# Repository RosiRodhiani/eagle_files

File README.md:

eagle_files
===========

THE SOFTWARE IS PROVIDED "AS IS", WITHOUT WARRANTY OF ANY KIND, EXPRESS OR IMPLIED, INCLUDING BUT NOT LIMITED TO THE WARRANTIES OF MERCHANTABILITY, FITNESS FOR A PARTICULAR PURPOSE AND NONINFRINGEMENT. IN NO EVENT SHALL THE AUTHORS OR COPYRIGHT HOLDERS BE LIABLE FOR ANY CLAIM, DAMAGES OR OTHER LIABILITY, WHETHER IN AN ACTION OF CONTRACT, TORT OR OTHERWISE, ARISING FROM, OUT OF OR IN CONNECTION WITH THE SOFTWARE OR THE USE OR OTHER DEALINGS IN THE SOFTWARE.

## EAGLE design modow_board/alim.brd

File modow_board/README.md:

A board I made for the french robotics cup of 2016 (beachbots).
It uses a Nucleo (stm32) as (mother board', the rest is mainly power and digital analog I/O.

The PRODUCT IS PROVIDED "AS IS", WITHOUT WARRANTY OF ANY KIND, EXPRESS OR IMPLIED, INCLUDING BUT NOT LIMITED TO THE WARRANTIES OF MERCHANTABILITY, FITNESS FOR A PARTICULAR PURPOSE AND NONINFRINGEMENT. IN NO EVENT SHALL THE AUTHORS OR COPYRIGHT HOLDERS BE LIABLE FOR ANY CLAIM, DAMAGES OR OTHER LIABILITY, WHETHER IN AN ACTION OF CONTRACT, TORT OR OTHERWISE, ARISING FROM, OUT OF OR IN CONNECTION WITH THE SOFTWARE OR THE USE OR OTHER DEALINGS IN THE PRODUCT.

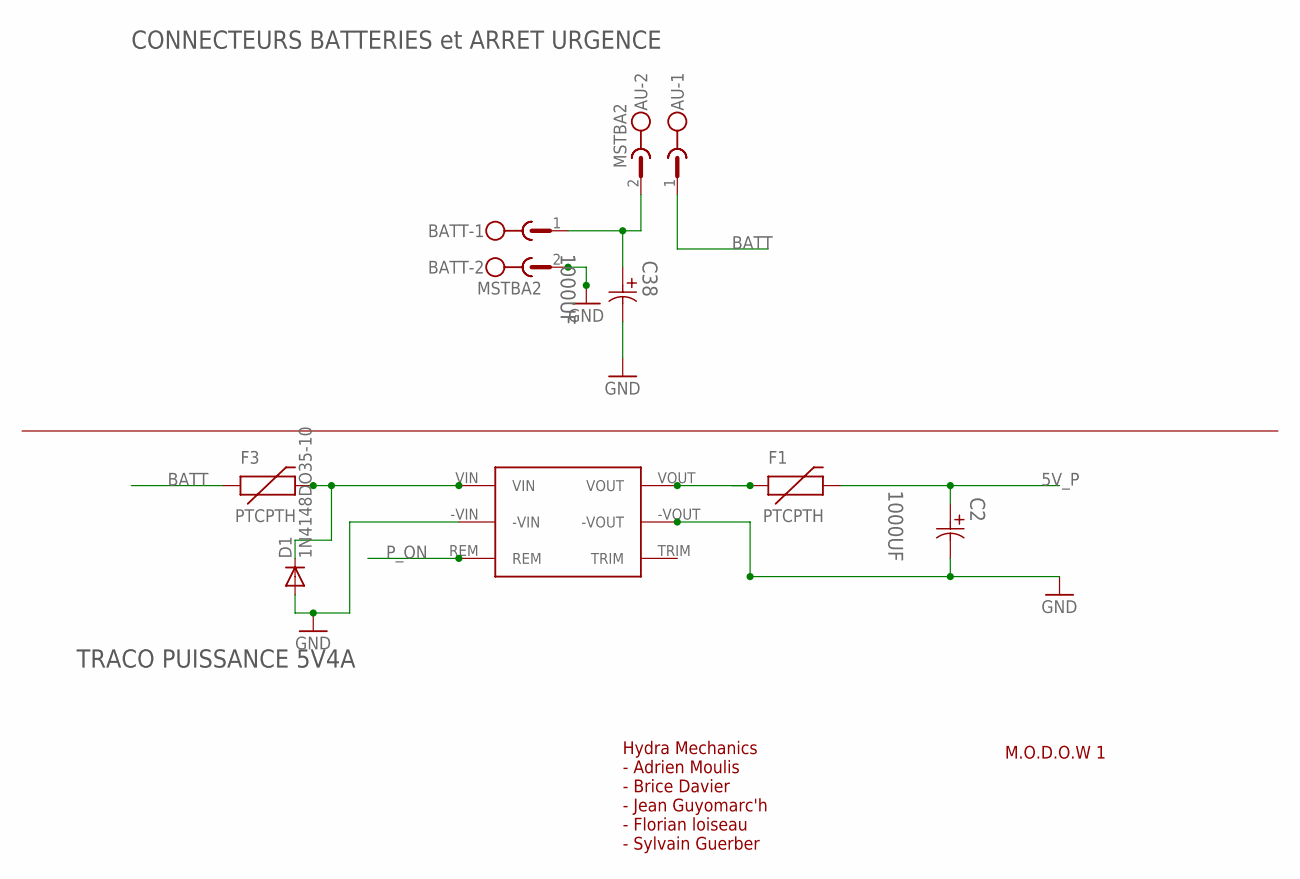
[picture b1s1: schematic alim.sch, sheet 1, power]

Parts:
AU: MSTBA2
BATT: MSTBA2
C2, C38: 1000UF; CAPPR500-1250X2700
D1: 1N4148DO35-10; DO35-10
F1, F3: PTCPTH; PTC
U$9: TEN202411WIN

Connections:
5V_P: C2.1, F1.P$2 (2); also elsewhere on the board
BATT: AU.1, F3.P$1 (1); also elsewhere on the board
GND: BATT.2, C2.2, C38.2, D1.A, U$9.-VIN, U$9.-VOUT; also elsewhere on the board
unnamed: F1.P$1 (1), U$9.VOUT
unnamed: AU.2, BATT.1, C38.1
unnamed: D1.C, F3.P$2 (2), U$9.VIN
P_ON: U$9.REM; also elsewhere on the board

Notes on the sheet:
Hydra Mechanics - Adrien Moulis - Brice Davier - Jean Guyomarc'h - Florian loiseau - Sylvain Guerber
M.O.D.O.W 1
CONNECTEURS BATTERIES et ARRET URGENCE
TRACO PUISSANCE 5V4A

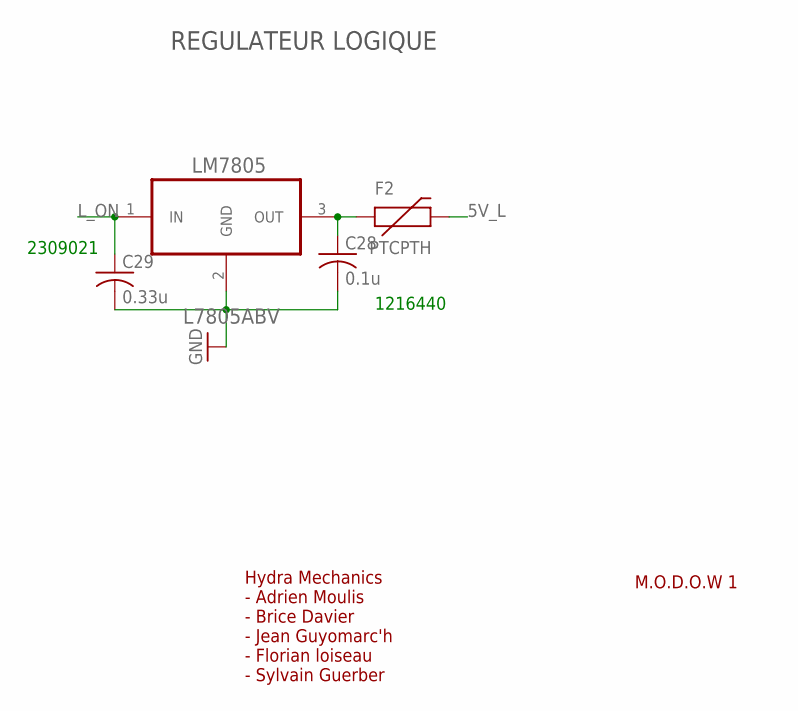
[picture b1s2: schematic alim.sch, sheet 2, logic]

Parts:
C28: 0.1u; C0805
C29: 0.33u; C0805
F2: PTCPTH; PTC
LM7805: L7805ABV; TO254P482X1024X3124-3P

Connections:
5V_L: F2.P$2 (2); also elsewhere on the board
GND: C28.2, C29.2, LM7805.2 (GND); also elsewhere on the board
L_ON: C29.1, LM7805.1 (IN); also elsewhere on the board
unnamed: C28.1, F2.P$1 (1), LM7805.3 (OUT)

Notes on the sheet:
Hydra Mechanics - Adrien Moulis - Brice Davier - Jean Guyomarc'h - Florian loiseau - Sylvain Guerber
M.O.D.O.W 1
REGULATEUR LOGIQUE
1216440
2309021

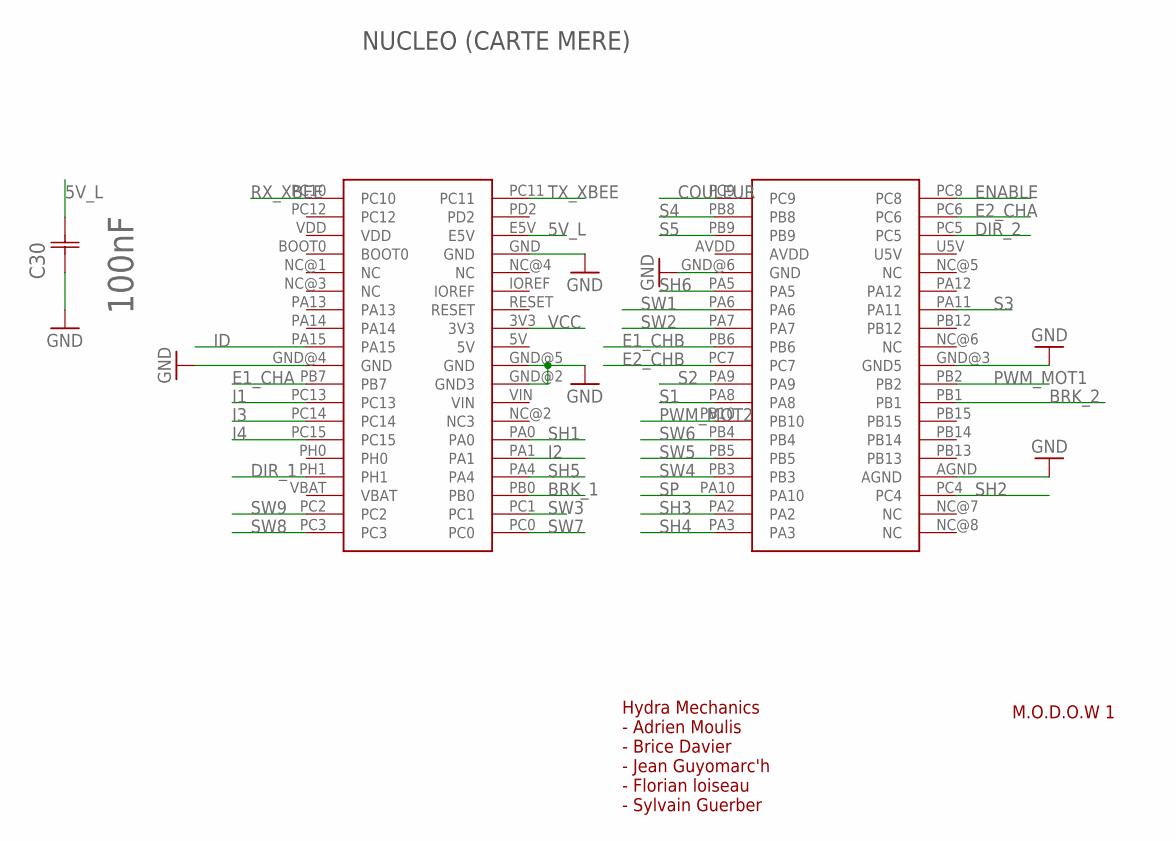
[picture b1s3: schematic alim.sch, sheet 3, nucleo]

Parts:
C30: 100nF; CAPC2013X95N
NUCLEO: NUCLEO-F446-RE-CON; NUCLEO-F446RE-CON

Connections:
5V_L: C30.2 (C2), NUCLEO.E5V; also elsewhere on the board
BRK_1: NUCLEO.PB0; also elsewhere on the board
BRK_2: NUCLEO.PB1; also elsewhere on the board
COULEUR: NUCLEO.PC9; also elsewhere on the board
DIR_1: NUCLEO.PH1; also elsewhere on the board
DIR_2: NUCLEO.PC5; also elsewhere on the board
E1_CHA: NUCLEO.PB7; also elsewhere on the board
E1_CHB: NUCLEO.PB6; also elsewhere on the board
E2_CHA: NUCLEO.PC6; also elsewhere on the board
E2_CHB: NUCLEO.PC7; also elsewhere on the board
ENABLE: NUCLEO.PC8; also elsewhere on the board
GND: C30.1 (C1), NUCLEO.AGND, NUCLEO.GND, NUCLEO.GND@2 (GND3), NUCLEO.GND@3 (GND5), NUCLEO.GND@4 (GND), NUCLEO.GND@5 (GND), NUCLEO.GND@6 (GND); also elsewhere on the board
I1: NUCLEO.PC13; also elsewhere on the board
I2: NUCLEO.PA1; also elsewhere on the board
I3: NUCLEO.PC14; also elsewhere on the board
I4: NUCLEO.PC15; also elsewhere on the board
ID: NUCLEO.PA15; also elsewhere on the board
PWM_MOT1: NUCLEO.PB2; also elsewhere on the board
PWM_MOT2: NUCLEO.PB10; also elsewhere on the board
RX_XBEE: NUCLEO.PC10; also elsewhere on the board
S1: NUCLEO.PA8; also elsewhere on the board
S2: NUCLEO.PA9; also elsewhere on the board
S3: NUCLEO.PA11; also elsewhere on the board
S4: NUCLEO.PB8; also elsewhere on the board
S5: NUCLEO.PB9; also elsewhere on the board
SH1: NUCLEO.PA0; also elsewhere on the board
SH2: NUCLEO.PC4; also elsewhere on the board
SH3: NUCLEO.PA2; also elsewhere on the board
SH4: NUCLEO.PA3; also elsewhere on the board
SH5: NUCLEO.PA4; also elsewhere on the board
SH6: NUCLEO.PA5; also elsewhere on the board
SP: NUCLEO.PA10; also elsewhere on the board
SW1: NUCLEO.PA6; also elsewhere on the board
SW2: NUCLEO.PA7; also elsewhere on the board
SW3: NUCLEO.PC1; also elsewhere on the board
SW4: NUCLEO.PB3; also elsewhere on the board
SW5: NUCLEO.PB5; also elsewhere on the board
SW6: NUCLEO.PB4; also elsewhere on the board
SW7: NUCLEO.PC0; also elsewhere on the board
SW8: NUCLEO.PC3; also elsewhere on the board
SW9: NUCLEO.PC2; also elsewhere on the board
TX_XBEE: NUCLEO.PC11; also elsewhere on the board
VCC: NUCLEO.3V3; also elsewhere on the board

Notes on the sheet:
Hydra Mechanics - Adrien Moulis - Brice Davier - Jean Guyomarc'h - Florian loiseau - Sylvain Guerber
M.O.D.O.W 1
NUCLEO (CARTE MERE)

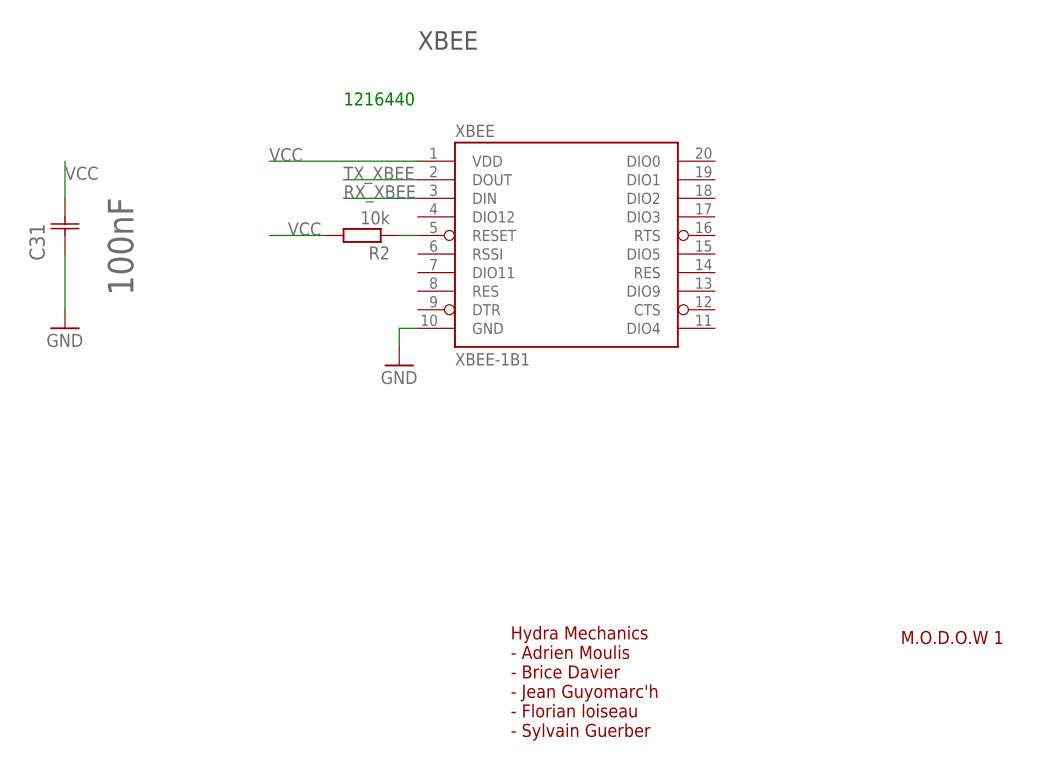
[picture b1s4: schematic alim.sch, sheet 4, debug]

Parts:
C31: 100nF; CAPC2013X95N
R2: 10k; 0207/7
XBEE: XBEE-1B1; XBEE-1

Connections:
GND: C31.1 (C1), XBEE.10 (GND); also elsewhere on the board
unnamed: R2.1, XBEE.5 (RESET)
RX_XBEE: XBEE.3 (DIN); also elsewhere on the board
TX_XBEE: XBEE.2 (DOUT); also elsewhere on the board
VCC: C31.2 (C2), R2.2, XBEE.1 (VDD); also elsewhere on the board

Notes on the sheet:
Hydra Mechanics - Adrien Moulis - Brice Davier - Jean Guyomarc'h - Florian loiseau - Sylvain Guerber
M.O.D.O.W 1
XBEE
1216440

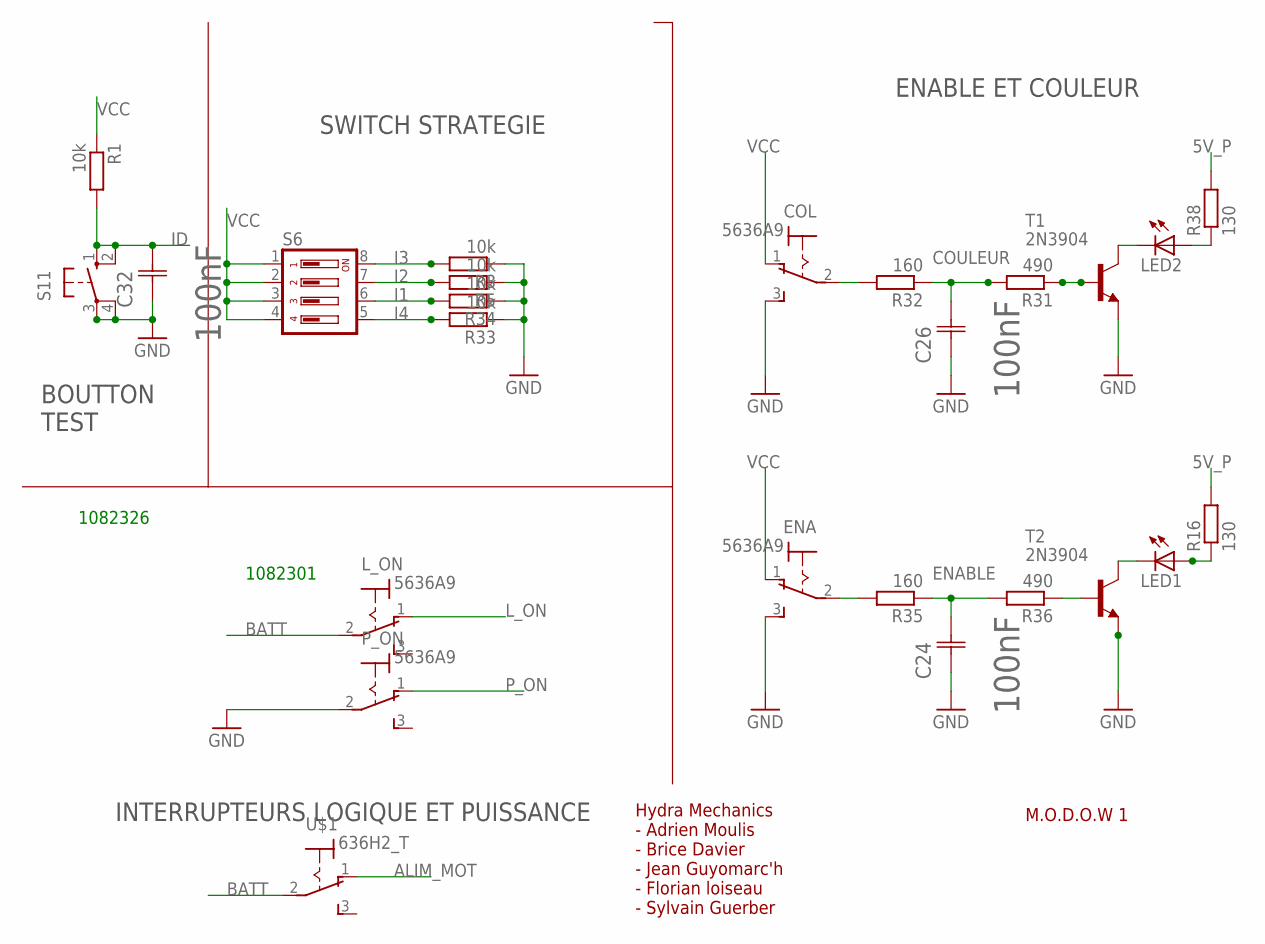
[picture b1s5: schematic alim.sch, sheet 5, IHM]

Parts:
C24, C26, C32: 100nF; CAPC2013X95N
COL: 5636A9
ENA: 5636A9
LED1, LED2: LED3MM
L_ON: 5636A9
P_ON: 5636A9
R1, R3, R5, R33, R34: 10k; 0207/7
R16, R38: 130; 0207/7
R31, R36: 490; 0207/7
R32, R35: 160; 0207/7
S6: DS04; DS-04
S11: 10-XX; B3F-10XX
T1, T2: 2N3904; TO92
U$1: 636H2_T; 636H2

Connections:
5V_P: R16.2, R38.2; also elsewhere on the board
ALIM_MOT: U$1.1 (O); also elsewhere on the board
BATT: L_ON.2, U$1.2; also elsewhere on the board
COULEUR: C26.2 (C2), R31.2, R32.1; also elsewhere on the board
ENABLE: C24.2 (C2), R35.1, R36.2; also elsewhere on the board
GND: C24.1 (C1), C26.1 (C1), C32.1 (C1), COL.3 (S), ENA.3 (S), P_ON.2, R3.1, R5.1, R33.1, R34.1, S11.3, S11.4 (P1), T1.3 (E), T2.3 (E); also elsewhere on the board
I1: R34.2, S6.6; also elsewhere on the board
I2: R5.2, S6.7; also elsewhere on the board
I3: R3.2, S6.8; also elsewhere on the board
I4: R33.2, S6.5; also elsewhere on the board
ID: C32.2 (C2), R1.2, S11.1 (S), S11.2 (S1); also elsewhere on the board
L_ON: L_ON.1 (O); also elsewhere on the board
unnamed: LED1.K (C), T2.1 (C)
unnamed: R36.1, T2.2 (B)
unnamed: LED2.A, R38.1
unnamed: COL.2, R32.2
unnamed: R31.1, T1.2 (B)
unnamed: ENA.2, R35.2
unnamed: LED1.A, R16.1
unnamed: LED2.K (C), T1.1 (C)
P_ON: P_ON.1 (O); also elsewhere on the board
VCC: COL.1 (O), ENA.1 (O), R1.1, S6.1, S6.2, S6.3, S6.4; also elsewhere on the board

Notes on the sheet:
Hydra Mechanics - Adrien Moulis - Brice Davier - Jean Guyomarc'h - Florian loiseau - Sylvain Guerber
M.O.D.O.W 1
SWITCH STRATEGIE
INTERRUPTEURS LOGIQUE ET PUISSANCE
ENABLE ET COULEUR
BOUTTON TEST
1082326
1082301

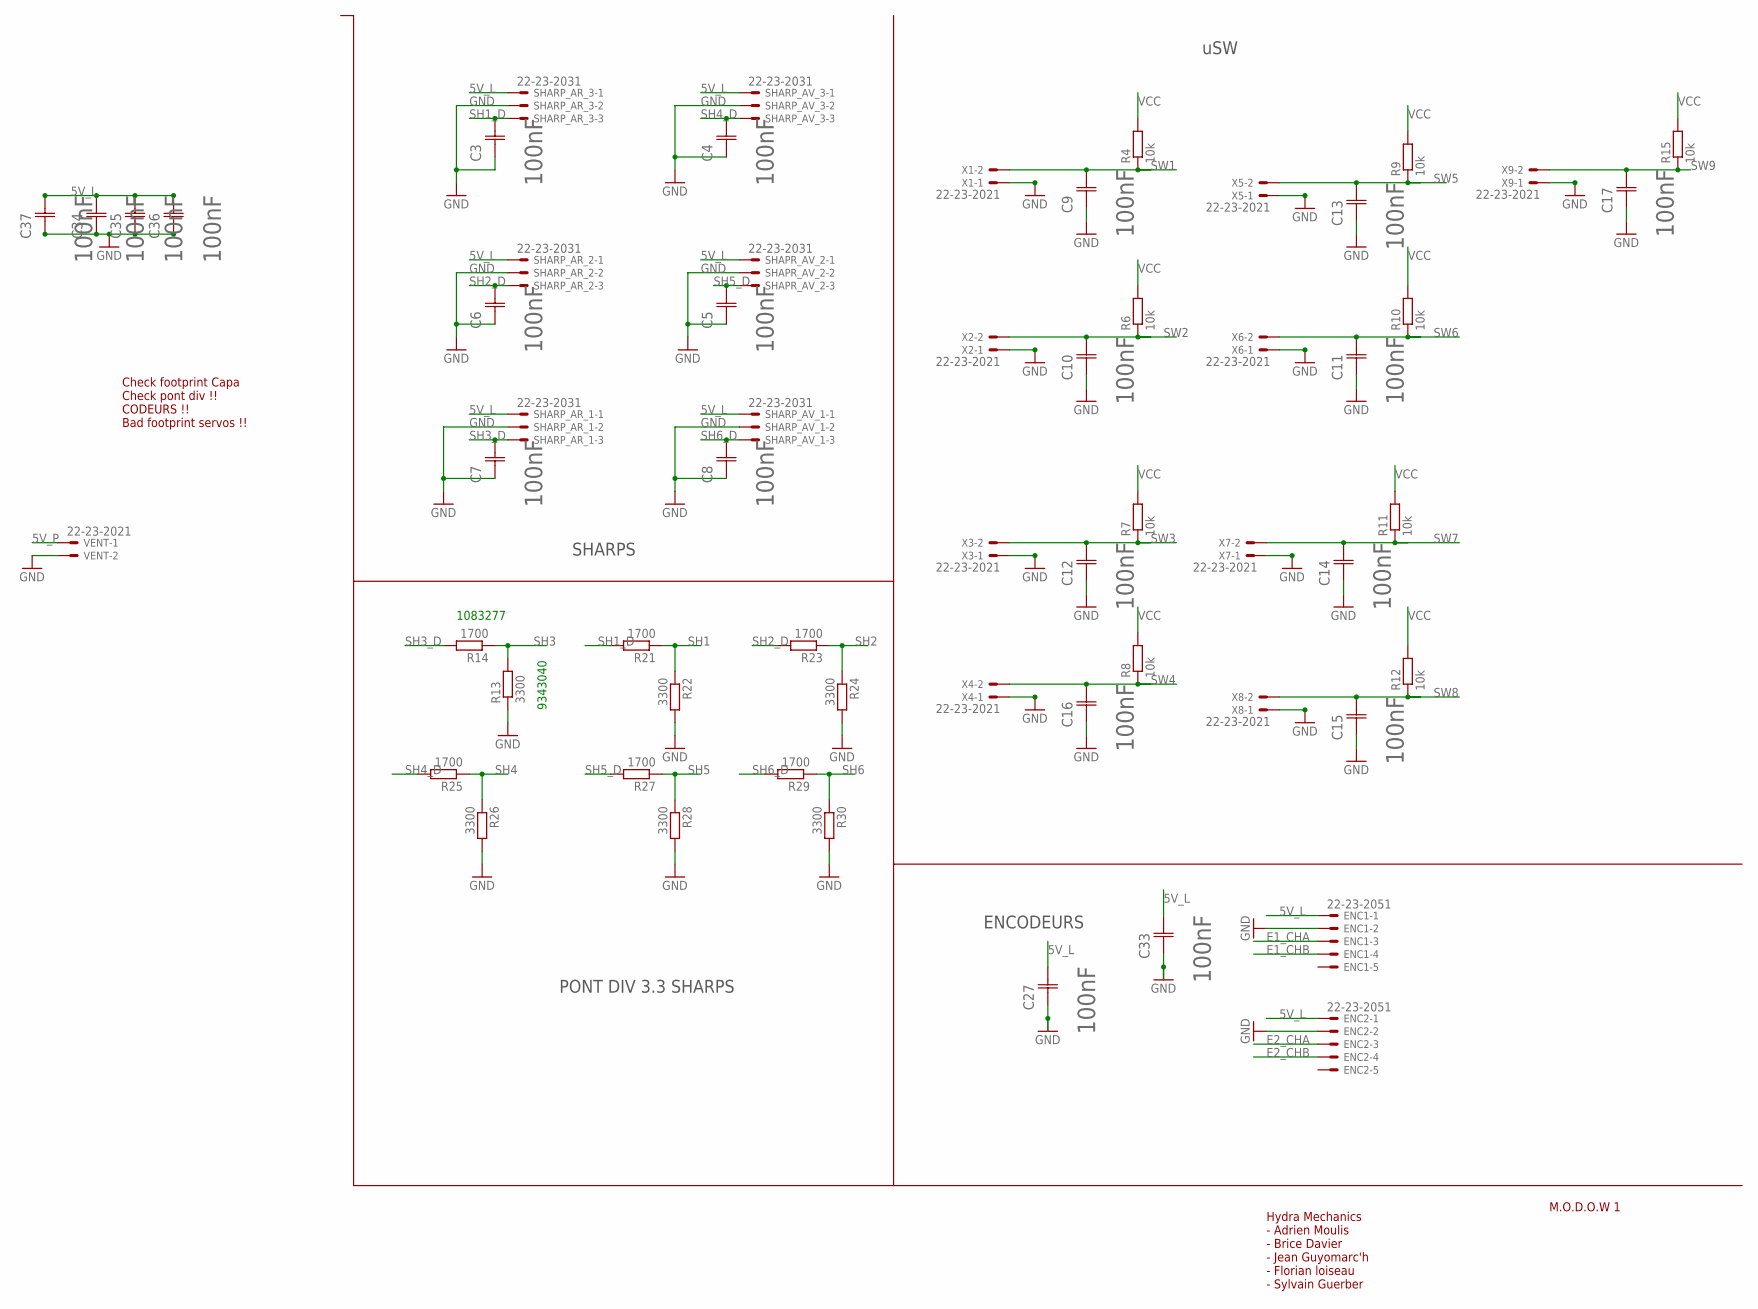
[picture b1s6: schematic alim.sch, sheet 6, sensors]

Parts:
C3, C4, C5, C6, C7, C8, C9, C10, C11, C12, C13, C14, C15, C16, C17, C27, C33, C34, C35, C36, C37: 100nF; CAPC2013X95N
ENC1, ENC2: 22-23-2051
R4, R6, R7, R8, R9, R10, R11, R12, R15: 10k; 0207/7
R13, R22, R24, R26, R28, R30: 3300; 0207/7
R14, R21, R23, R25, R27, R29: 1700; 0207/7
SHAPR_AV_2: 22-23-2031
SHARP_AR_1, SHARP_AR_2, SHARP_AR_3: 22-23-2031
SHARP_AV_1, SHARP_AV_3: 22-23-2031
VENT: 22-23-2021
X1, X2, X3, X4, X5, X6, X7, X8, X9: 22-23-2021

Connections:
5V_L: C27.2 (C2), C33.2 (C2), C34.2 (C2), C35.2 (C2), C36.2 (C2), C37.2 (C2), ENC1.1, ENC2.1, SHAPR_AV_2.1, SHARP_AR_1.1, SHARP_AR_2.1, SHARP_AR_3.1, SHARP_AV_1.1, SHARP_AV_3.1; also elsewhere on the board
5V_P: VENT.1; also elsewhere on the board
E1_CHA: ENC1.3; also elsewhere on the board
E1_CHB: ENC1.4; also elsewhere on the board
E2_CHA: ENC2.3; also elsewhere on the board
E2_CHB: ENC2.4; also elsewhere on the board
GND: C3.1 (C1), C4.1 (C1), C5.1 (C1), C6.1 (C1), C7.1 (C1), C8.1 (C1), C9.1 (C1), C10.1 (C1), C11.1 (C1), C12.1 (C1), C13.1 (C1), C14.1 (C1), C15.1 (C1), C16.1 (C1), C17.1 (C1), C27.1 (C1), C33.1 (C1), C34.1 (C1), C35.1 (C1), C36.1 (C1), C37.1 (C1), ENC1.2, ENC2.2, R13.1, R22.2, R24.2, R26.2, R28.2, R30.2, SHAPR_AV_2.2, SHARP_AR_1.2, SHARP_AR_2.2, SHARP_AR_3.2, SHARP_AV_1.2, SHARP_AV_3.2, VENT.2, X1.1, X2.1, X3.1, X4.1, X5.1, X6.1, X7.1, X8.1, X9.1; also elsewhere on the board
SH1: R21.1, R22.1; also elsewhere on the board
SH1_D: C3.2 (C2), R21.2, SHARP_AR_3.3
SH2: R23.1, R24.1; also elsewhere on the board
SH2_D: C6.2 (C2), R23.2, SHARP_AR_2.3
SH3: R13.2, R14.1; also elsewhere on the board
SH3_D: C7.2 (C2), R14.2, SHARP_AR_1.3
SH4: R25.1, R26.1; also elsewhere on the board
SH4_D: C4.2 (C2), R25.2, SHARP_AV_3.3
SH5: R27.1, R28.1; also elsewhere on the board
SH5_D: C5.2 (C2), R27.2, SHAPR_AV_2.3
SH6: R29.1, R30.1; also elsewhere on the board
SH6_D: C8.2 (C2), R29.2, SHARP_AV_1.3
SW1: C9.2 (C2), R4.1, X1.2; also elsewhere on the board
SW2: C10.2 (C2), R6.1, X2.2; also elsewhere on the board
SW3: C12.2 (C2), R7.1, X3.2; also elsewhere on the board
SW4: C16.2 (C2), R8.1, X4.2; also elsewhere on the board
SW5: C13.2 (C2), R9.1, X5.2; also elsewhere on the board
SW6: C11.2 (C2), R10.1, X6.2; also elsewhere on the board
SW7: C14.2 (C2), R11.1, X7.2; also elsewhere on the board
SW8: C15.2 (C2), R12.1, X8.2; also elsewhere on the board
SW9: C17.2 (C2), R15.1, X9.2; also elsewhere on the board
VCC: R4.2, R6.2, R7.2, R8.2, R9.2, R10.2, R11.2, R12.2, R15.2; also elsewhere on the board

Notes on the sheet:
Check footprint Capa Check pont div !! CODEURS !! Bad footprint servos !!
Hydra Mechanics - Adrien Moulis - Brice Davier - Jean Guyomarc'h - Florian loiseau - Sylvain Guerber
M.O.D.O.W 1
SHARPS
PONT DIV 3.3 SHARPS
ENCODEURS
uSW
9343040
1083277

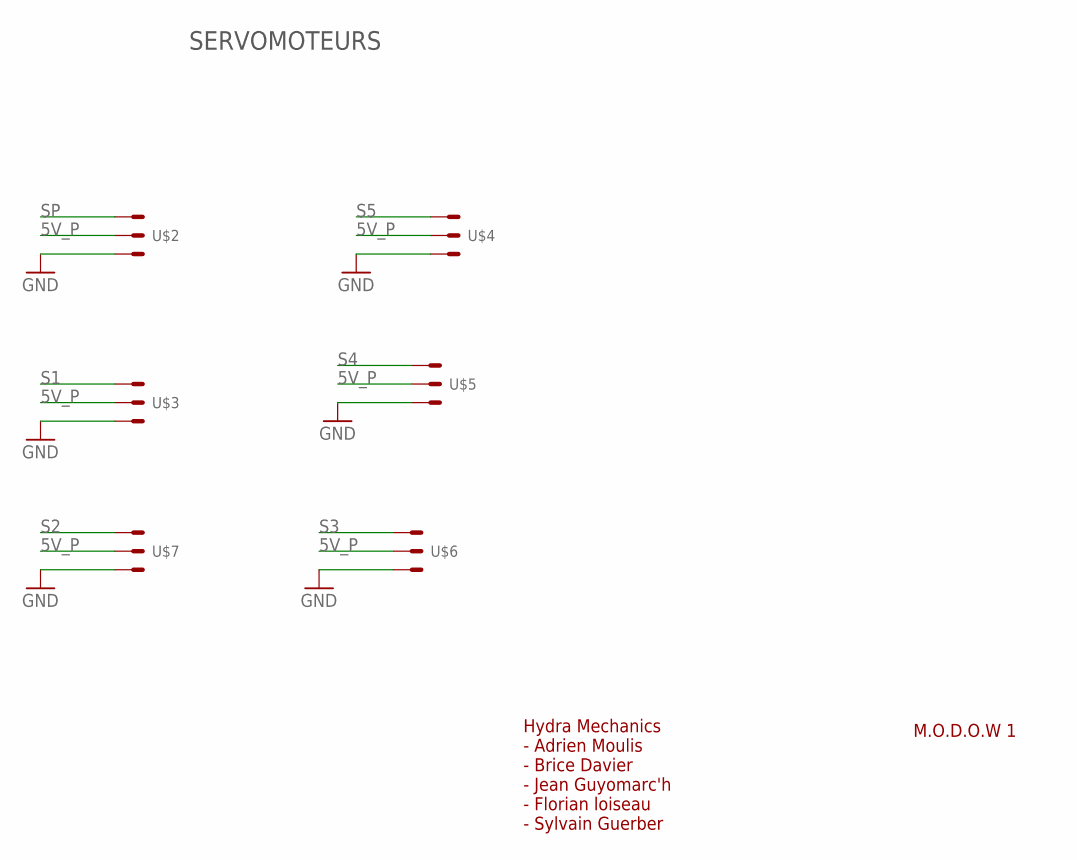
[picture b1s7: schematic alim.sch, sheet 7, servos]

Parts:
U$2, U$3, U$4, U$5, U$6, U$7: BA_HEADER_3P

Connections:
5V_P: U$2.P$2 (S2), U$3.P$2 (S2), U$4.P$2 (S2), U$5.P$2 (S2), U$6.P$2 (S2), U$7.P$2 (S2); also elsewhere on the board
GND: U$2.P$3 (S3), U$3.P$3 (S3), U$4.P$3 (S3), U$5.P$3 (S3), U$6.P$3 (S3), U$7.P$3 (S3); also elsewhere on the board
S1: U$3.P$1 (S1); also elsewhere on the board
S2: U$7.P$1 (S1); also elsewhere on the board
S3: U$6.P$1 (S1); also elsewhere on the board
S4: U$5.P$1 (S1); also elsewhere on the board
S5: U$4.P$1 (S1); also elsewhere on the board
SP: U$2.P$1 (S1); also elsewhere on the board

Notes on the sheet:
Hydra Mechanics - Adrien Moulis - Brice Davier - Jean Guyomarc'h - Florian loiseau - Sylvain Guerber
M.O.D.O.W 1
SERVOMOTEURS

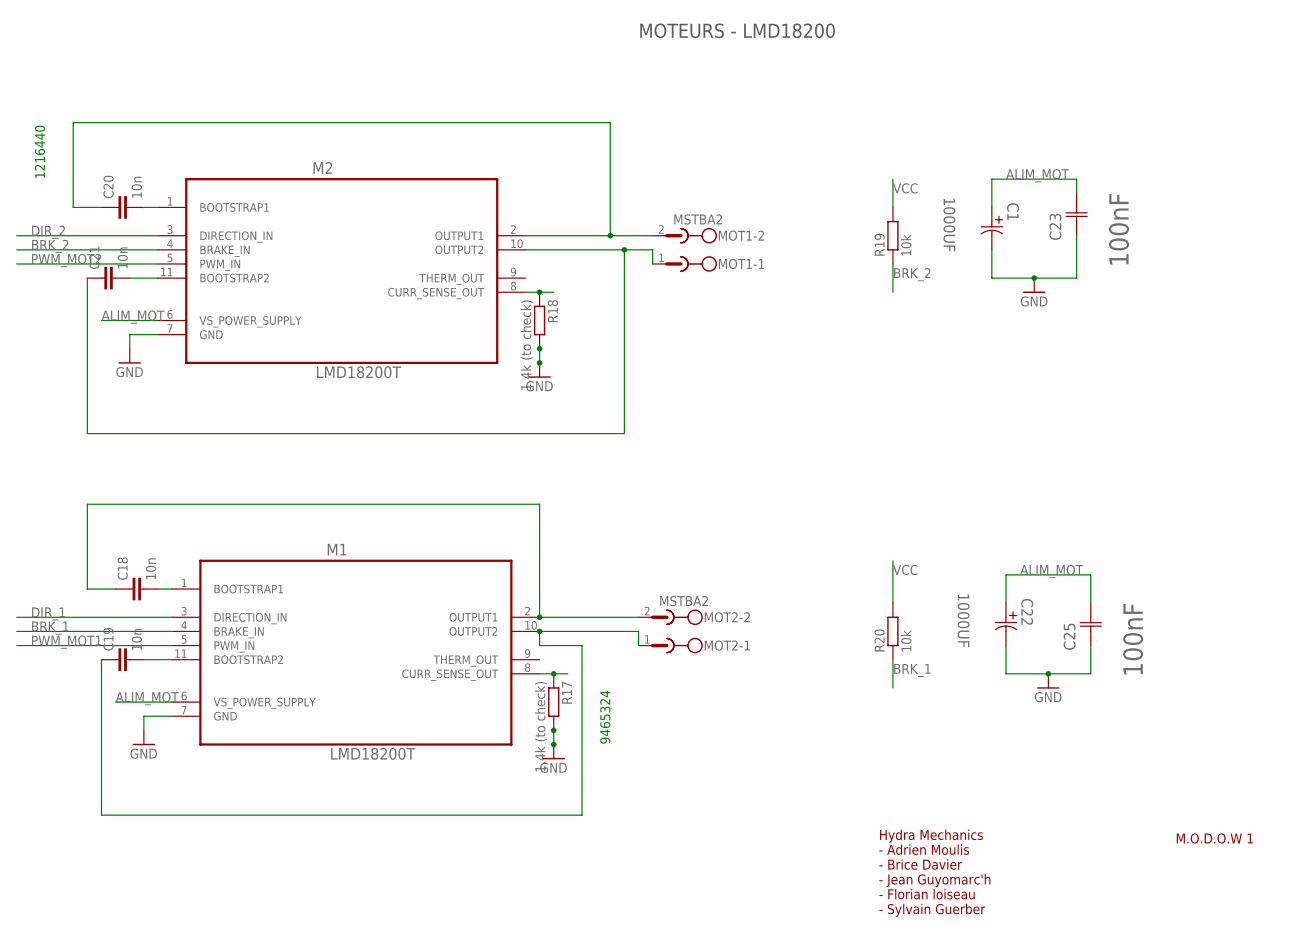
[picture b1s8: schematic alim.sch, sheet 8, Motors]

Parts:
C1, C22: 1000UF; CAPPR500-1250X2700
C18, C19, C20, C21: 10n; C025-024X044
C23, C25: 100nF; CAPC2013X95N
M1, M2: LMD18200T; DIOB_LMD18200T
MOT1, MOT2: MSTBA2
R17, R18: 1.4k (to check); 0207/7
R19, R20: 10k; 0207/7

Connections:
ALIM_MOT: C1.1, C22.1, C23.2 (C2), C25.2 (C2), M1.6 (VS_POWER_SUPPLY), M2.6 (VS_POWER_SUPPLY); also elsewhere on the board
BRK_1: M1.4 (BRAKE_IN), R20.1; also elsewhere on the board
BRK_2: M2.4 (BRAKE_IN), R19.1; also elsewhere on the board
DIR_1: M1.3 (DIRECTION_IN); also elsewhere on the board
DIR_2: M2.3 (DIRECTION_IN); also elsewhere on the board
GND: C1.2, C22.2, C23.1 (C1), C25.1 (C1), M1.7 (GND), M2.7 (GND), R17.2, R18.2; also elsewhere on the board
unnamed: C18.2, M1.1 (BOOTSTRAP1)
unnamed: M1.8 (CURR_SENSE_OUT), R17.1
unnamed: C19.2, M1.11 (BOOTSTRAP2)
unnamed: C18.1, M1.2 (OUTPUT1), MOT2.2
unnamed: C19.1, M1.10 (OUTPUT2), MOT2.1
unnamed: M2.8 (CURR_SENSE_OUT), R18.1
unnamed: C20.2, M2.1 (BOOTSTRAP1)
unnamed: C21.2, M2.11 (BOOTSTRAP2)
unnamed: C20.1, M2.2 (OUTPUT1), MOT1.2
unnamed: C21.1, M2.10 (OUTPUT2), MOT1.1
PWM_MOT1: M1.5 (PWM_IN); also elsewhere on the board
PWM_MOT2: M2.5 (PWM_IN); also elsewhere on the board
VCC: R19.2, R20.2; also elsewhere on the board

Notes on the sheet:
Hydra Mechanics - Adrien Moulis - Brice Davier - Jean Guyomarc'h - Florian loiseau - Sylvain Guerber
M.O.D.O.W 1
MOTEURS - LMD18200
9465324
1216440

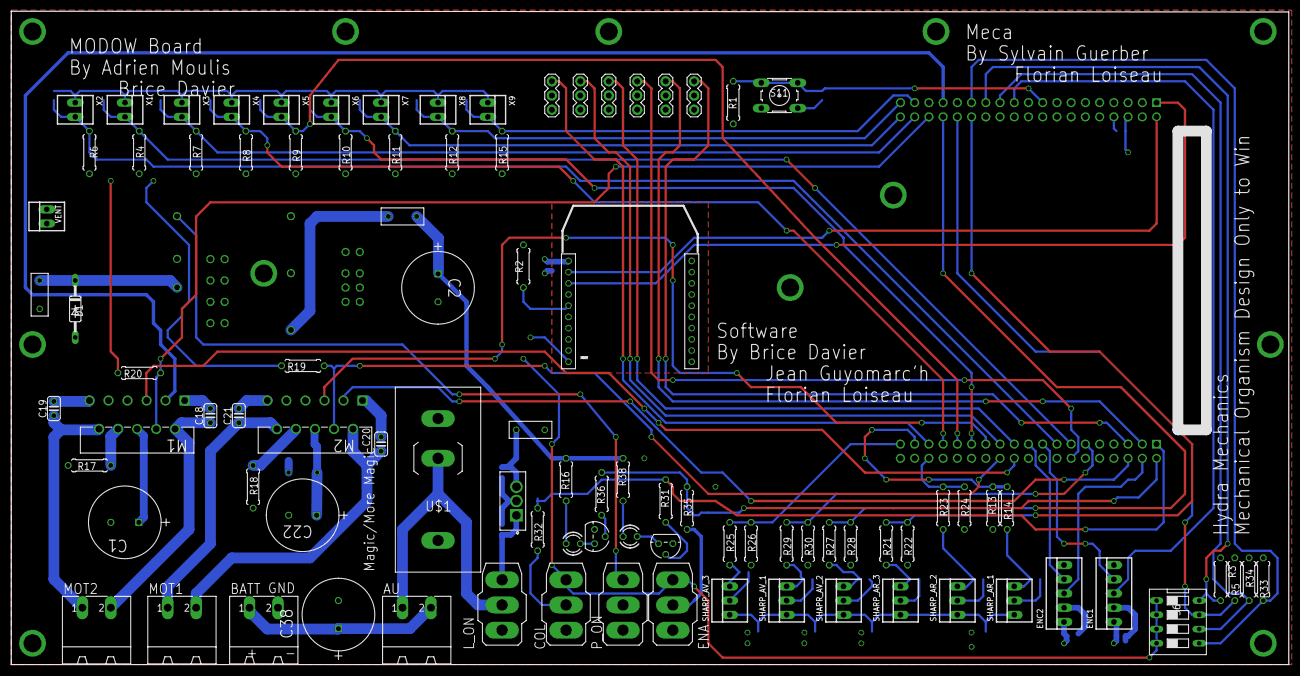
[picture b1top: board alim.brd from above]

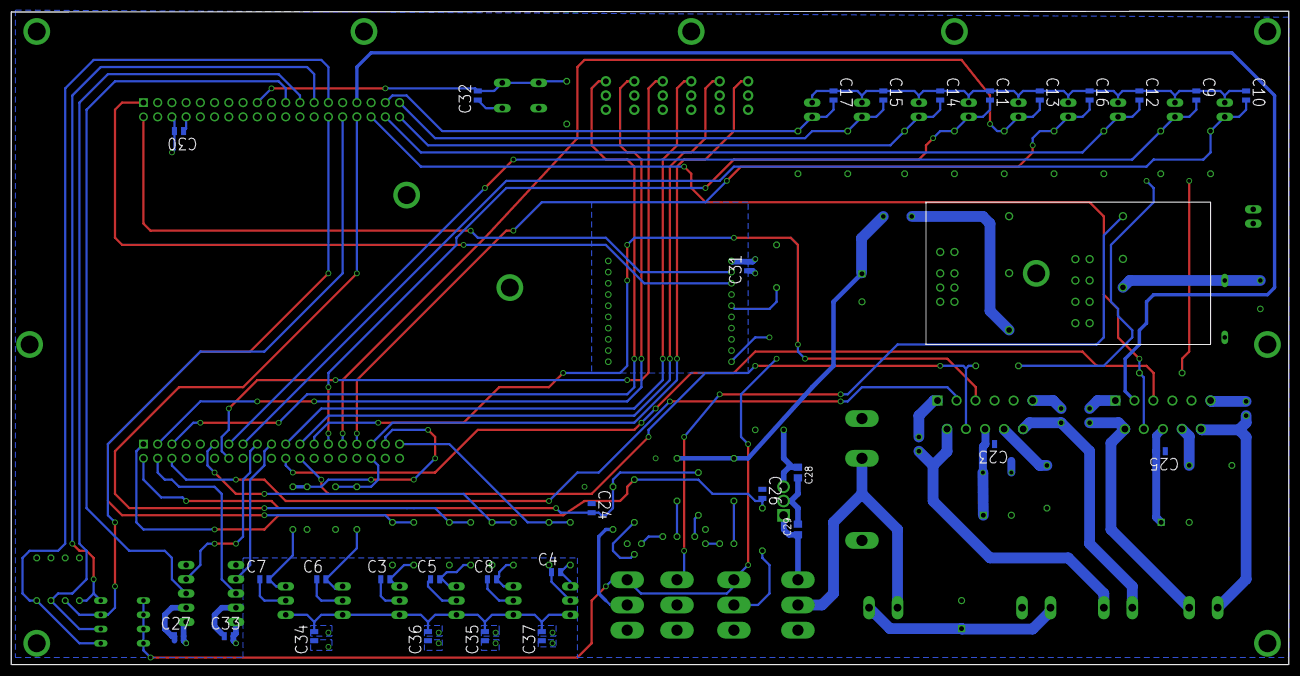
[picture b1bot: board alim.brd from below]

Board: 4 copper layers, 228.1 x 116.7 mm, 124 parts (30 on the bottom side), 77 nets.

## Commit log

2014-12-19 vchanged name pin 17
2014-12-19 arduino uno lib v1
2014-12-27 library for MQ-135 gaz sensor
2014-12-27 library for jtag ice2 atmega
2014-12-27 library for light sensor opt101
2014-12-27 upadted general readme
2014-12-27 mispelled correction in readme
2015-01-11 removed con-jtag lib
2015-01-11 added new library con-misc with breal away headers and atmel jtag connectors
2016-09-24 traco library
2016-09-24 xbee library
2016-09-24 switch library
2016-09-24 nucleo library
2016-09-24 modow board, an lecetronic board for 2016 french robotic cup. The robot was called modow. It is to be noted that it is missing two pull-up/pull-down resistors on the LM18200
